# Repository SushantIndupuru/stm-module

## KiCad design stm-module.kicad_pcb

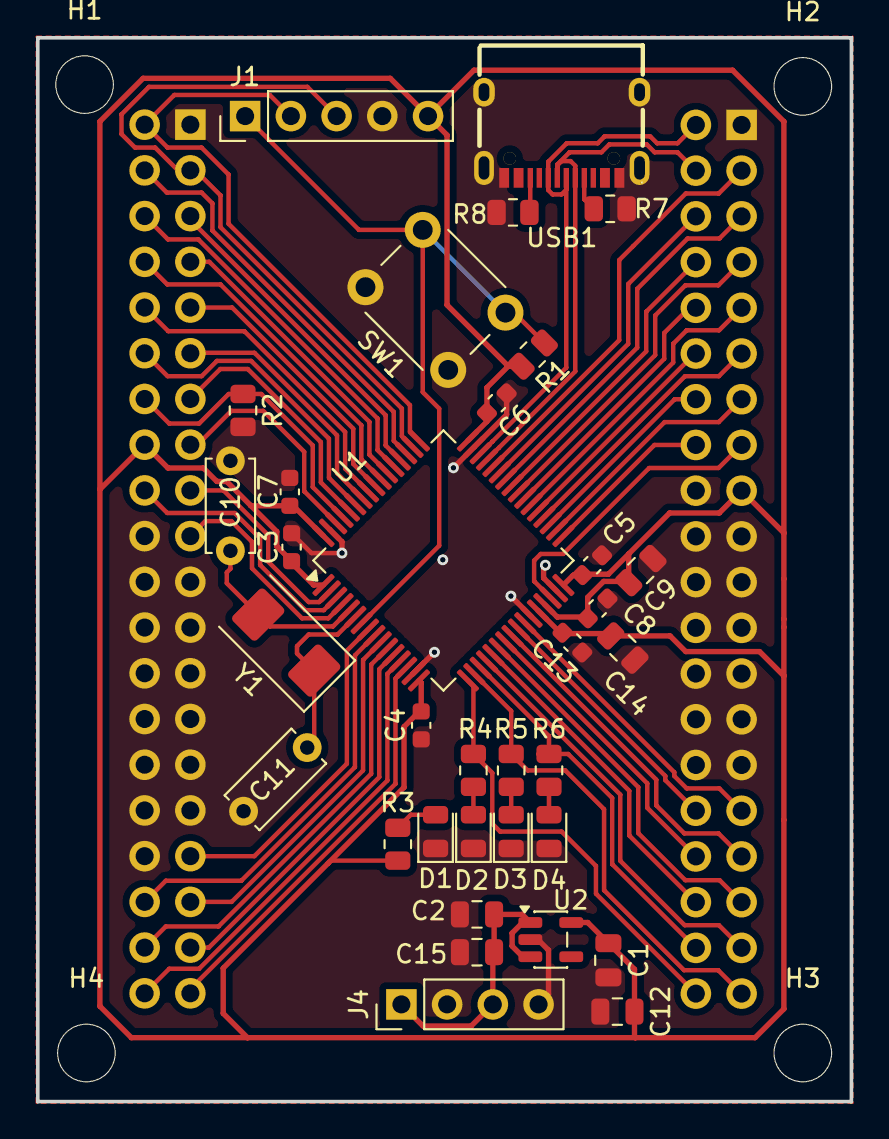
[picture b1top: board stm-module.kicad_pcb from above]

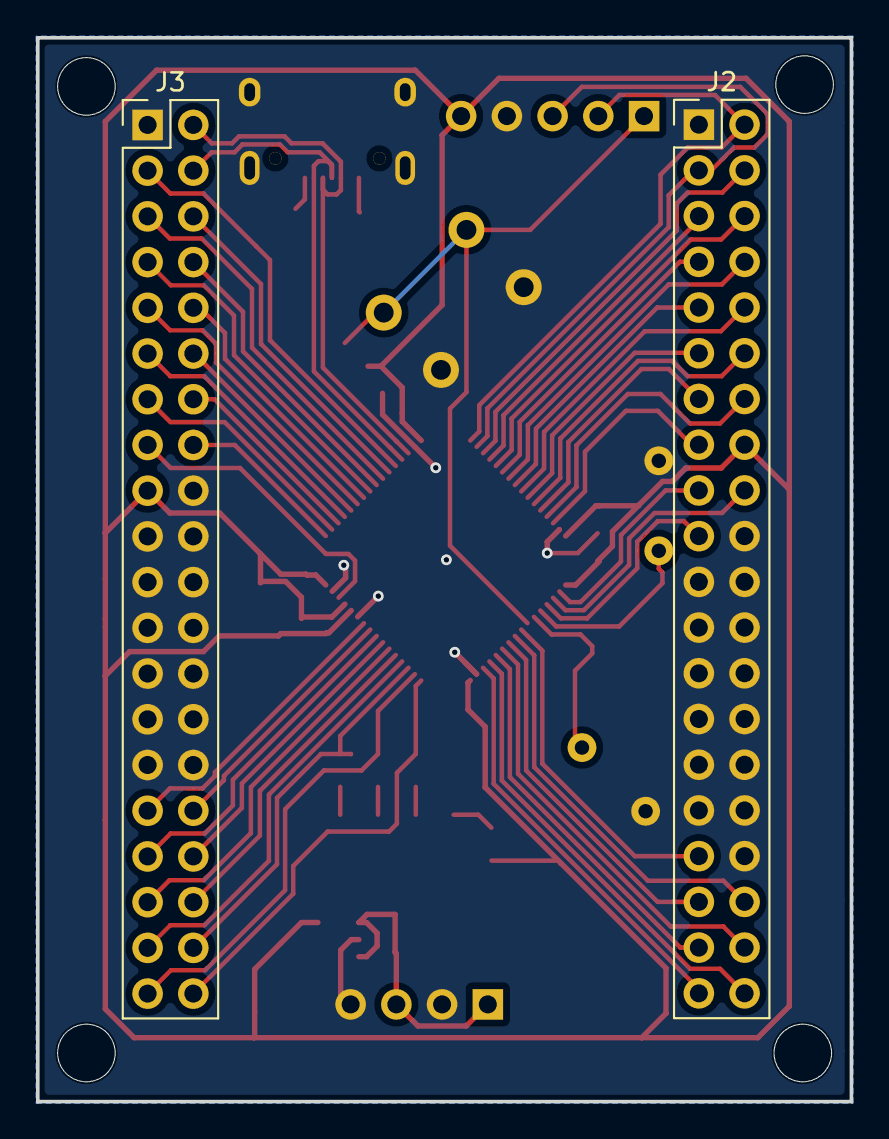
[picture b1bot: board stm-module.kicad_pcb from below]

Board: 2 copper layers, 45.2 x 59.1 mm, 40 parts (2 on the bottom side), 61 nets.

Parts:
C1, C2, C9, C14: 1uF; C_0805_2012Metric
C3, C4, C5, C6, C7, C8, C13: 100nF; C_0603_1608Metric
C10, C11: 15pF; C_Disc_D5.0mm_W2.5mm_P5.00mm
C12, C15: 10uF; C_0805_2012Metric
D1: PWR LED; LED_0805_2012Metric
D2: RUN LED; LED_0805_2012Metric
D3: CAN LED; LED_0805_2012Metric
D4: FAULT LED; LED_0805_2012Metric
H1, H2, H3, H4: MountingHole; MountingHole_3.2mm_M3
J1: Conn_01x05_Pin; PinHeader_1x05_P2.54mm_Vertical
J2: connectorL; PinHeader_2x20_P2.54mm_Vertical
J3: connectorR; PinHeader_2x20_P2.54mm_Vertical
J4: power; PinHeader_1x04_P2.54mm_Vertical
R1, R2: 10kΩ; R_0805_2012Metric
R3: 330Ω; R_0805_2012Metric
R4: 220Ω; R_0805_2012Metric
R5, R6: 1kΩ; R_0805_2012Metric
R7, R8: 5.1kΩ; R_0805_2012Metric
SW1: Reset; SW_PUSH_6mm
U1: STM32G474RETx; LQFP-64_10x10mm_P0.5mm
U2: TPS7A20xxxDBV; SOT-23-5
USB1: TYPE-C 16PIN 2MD; USB-C-SMD_TYPE-C-16PIN-2MD-073
Y1: Crystal; Crystal_SMD_0603-2Pin_6.0x3.5mm

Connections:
+3.3V: C1.1, C3.2, C4.2, C5.2, C6.2, C7.2, C8.2, C9.1, C12.1, C13.2, C14.2, J1.5, J2.16, J3.17, R1.1, R3.1, U1.1 (VBAT), U1.16 (VDD), U1.28 (VREF+), U1.29 (VDDA), U1.32 (VDD), U1.48 (VDD), U1.64 (VDD), U2.5 (OUT)
+5V: C2.1, C15.1, J4.1, J4.3, U2.1 (IN), U2.3 (EN)
/D+: J3.2, U1.46 (PA12), USB1.A6 (Dp1), USB1.B6 (Dp2)
/D-: J3.4, U1.45 (PA11), USB1.A7 (Dn1), USB1.B7 (Dn2)
/NRST: J1.1, R1.2, SW1.2, U1.7 (PG10)
/PA0: J2.37, U1.12 (PA0)
/PA1: J2.40, U1.13 (PA1)
/PA2: J2.39, U1.14 (PA2)
/PA3: J3.40, R4.1, U1.17 (PA3)
/PA4: J3.39, R5.1, U1.18 (PA4)
/PA5: J3.38, R6.1, U1.19 (PA5)
/PA6: J3.37, U1.20 (PA6)
/PA7: J3.36, U1.21 (PA7)
/PA8: J3.5, U1.42 (PA8)
/PA9: J3.6, U1.43 (PA9)
/PA10: J3.3, U1.44 (PA10)
/PA13: J1.2, J2.2, U1.49 (PA13)
/PA14: J1.3, J2.3, U1.50 (PA14)
/PA15: J2.4, U1.51 (PA15)
/PB0: J3.33, U1.24 (PB0)
/PB1: J3.32, U1.25 (PB1)
/PB2: J3.31, U1.26 (PB2)
/PB3: J2.9, U1.56 (PB3)
/PB4: J2.10, U1.57 (PB4)
/PB5: J2.11, U1.58 (PB5)
/PB6: J2.12, U1.59 (PB6)
/PB7: J2.13, U1.60 (PB7)
/PB8: J2.14, R2.1, U1.61 (PB8)
/PB9: J2.15, U1.62 (PB9)
/PB10: J3.15, U1.30 (PB10)
/PB11: J3.16, U1.33 (PB11)
/PB12: J3.13, U1.34 (PB12)
/PB13: J3.14, U1.35 (PB13)
/PB14: J3.11, U1.36 (PB14)
/PB15: J3.12, U1.37 (PB15)
/PC0: J2.33, U1.8 (PC0)
/PC1: J2.36, U1.9 (PC1)
/PC2: J2.35, U1.10 (PC2)
/PC3: J2.38, U1.11 (PC3)
/PC4: J3.35, U1.22 (PC4)
/PC5: J3.34, U1.23 (PC5)
/PC6: J3.9, U1.38 (PC6)
/PC7: J3.10, U1.39 (PC7)
/PC8: J3.7, U1.40 (PC8)
/PC9: J3.8, U1.41 (PC9)
/PC10: J2.5, U1.52 (PC10)
/PC11: J2.6, U1.53 (PC11)
/PC12: J2.7, U1.54 (PC12)
/PC13: J2.17, U1.2 (PC13)
/PC14: J2.18, U1.3 (PC14)
/PC15: J2.19, U1.4 (PC15)
/PD2: J2.8, U1.55 (PD2)
GND: C1.2, C2.2, C3.1, C4.1, C5.1, C6.1, C7.1, C8.1, C9.2, C10.1, C11.1, C12.2, C13.1, C14.1, C15.2, D1.1 (K), D2.1 (K), D3.1 (K), D4.1 (K), J1.4, J2.1, J2.20, J2.21, J2.22, J2.23, J2.24, J2.25, J2.26, J2.27, J2.28, J2.29, J2.30, J2.31, J2.32, J2.34, J3.1, J3.18, J3.19, J3.20, J3.21, J3.22, J3.23, J3.24, J3.25, J3.26, J3.27, J3.28, J3.29, J3.30, J4.2, J4.4, R2.2, R7.1, R8.1, SW1.1, U1.15 (VSS), U1.27 (VSSA), U1.31 (VSS), U1.47 (VSS), U1.63 (VSS), U2.2 (GND), USB1.13 (EH), USB1.14 (EH), USB1.A1B12 (GND), USB1.B1A12 (GND)
unnamed: D1.2 (A), R3.2
unnamed: D2.2 (A), R4.2
unnamed: D3.2 (A), R5.2
unnamed: D4.2 (A), R6.2
unnamed: C10.2, U1.5 (PF0), Y1.2
unnamed: C11.2, U1.6 (PF1), Y1.1
unnamed: R7.2, USB1.A5 (CC1)
unnamed: R8.2, USB1.B5 (CC2)

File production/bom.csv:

Designator,Footprint,Quantity,Value,LCSC Part #
"C1, C14, C2, C9",0805,4,1uF,C107367
"C10, C11",C_Disc_D5.0mm_W2.5mm_P5.00mm,2,15pF,
"C12, C15",0805,2,10uF,C17024
"C13, C3, C4, C5, C6, C7, C8",0603,7,100nF,C1856507
D1,0805,1,PWR LED,C2297
D2,0805,1,RUN LED,C2293
D3,0805,1,CAN LED,C2296
D4,0805,1,FAULT LED,C2295
J1,PinHeader_1x05_P2.54mm_Vertical,1,Conn_01x05_Pin,
J2,PinHeader_2x20_P2.54mm_Vertical,1,connectorL,
J3,PinHeader_2x20_P2.54mm_Vertical,1,connectorR,
J4,PinHeader_1x04_P2.54mm_Vertical,1,power,
"R1, R2",0805,2,10kΩ,C17414
R3,0805,1,330Ω,C17630
R4,0805,1,220Ω,C17557
"R5, R6",0805,2,1kΩ,C17513
"R7, R8",0805,2,5.1kΩ,C27834
SW1,SW_PUSH_6mm,1,Reset,
U1,LQFP-64_10x10mm_P0.5mm,1,STM32G474RETx,C521608
U2,SOT-23-5,1,TPS7A20xxxDBV,C2862740
USB1,USB-C-SMD_TYPE-C-16PIN-2MD-073,1,TYPE-C 16PIN 2MD,C2765186
Y1,Crystal_SMD_0603-2Pin_6.0x3.5mm,1,Crystal,C18186341
